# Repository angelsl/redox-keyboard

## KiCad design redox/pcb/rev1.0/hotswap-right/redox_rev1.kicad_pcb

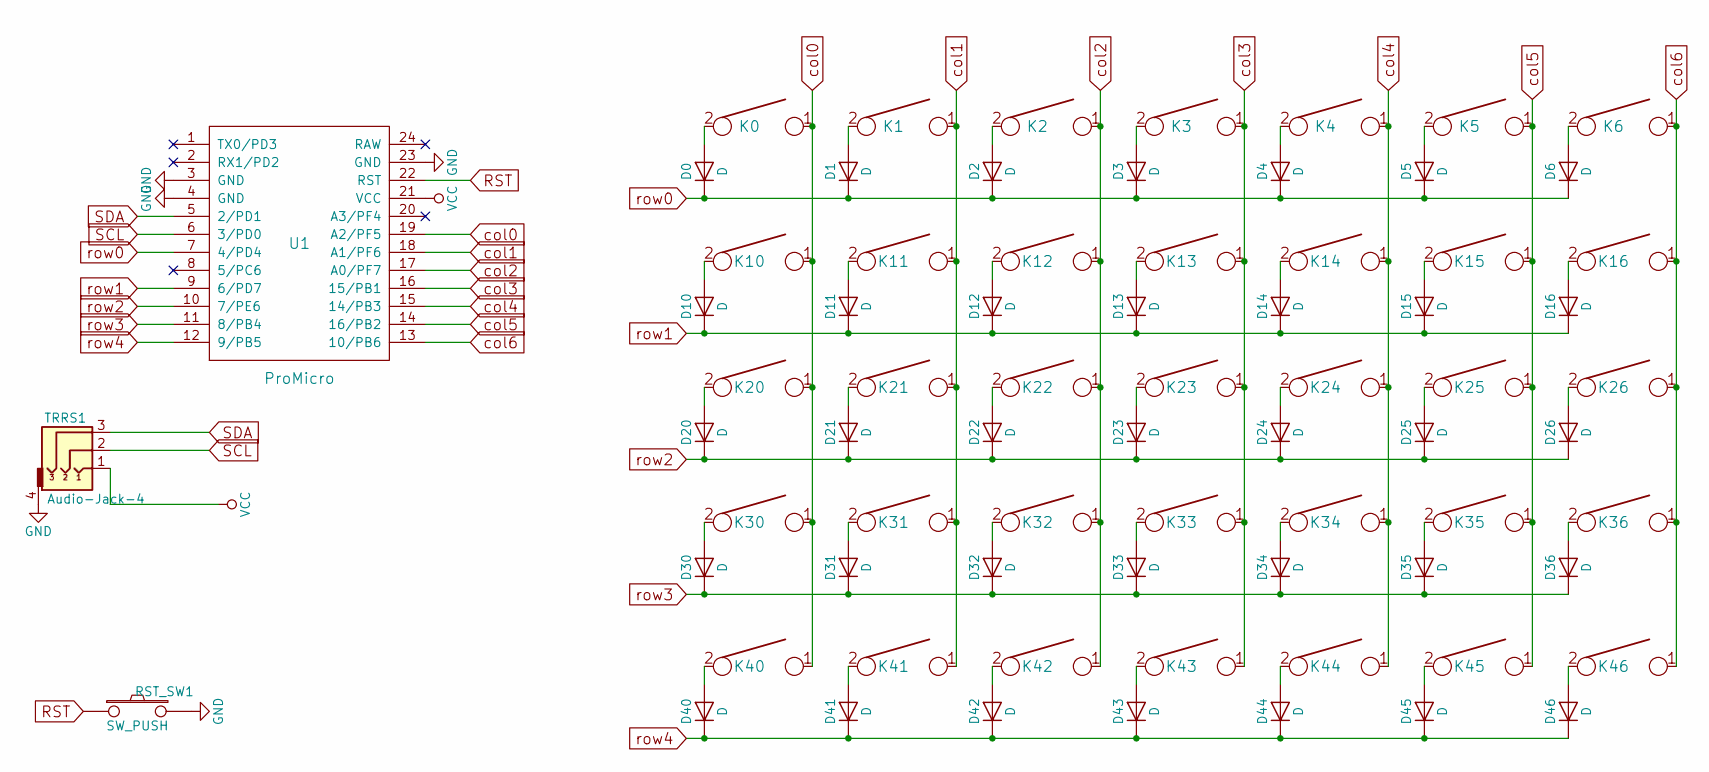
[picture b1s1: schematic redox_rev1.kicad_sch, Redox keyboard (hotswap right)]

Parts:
D0, D1, D2, D3, D4, D5, D6, D10, D11, D12, D13, D14, D15, D16, D20, D21, D22, D23, D24, D25, D26, D30, D31, D32, D33, D34, D35, D36, D40, D41, D42, D43, D44, D45, D46: D; Diode-smd-via
K0, K1, K2, K3, K4, K5, K6, K10, K11, K12, K13, K14, K15, K16, K20, K21, K22, K23, K24, K25, K26, K30, K31, K32, K33, K34, K35, K36, K40, K41, K42, K43, K44, K45, K46: KEYSW; Kailh_socket_MX
RST_SW1: SW_PUSH; SW_PUSH_6mm_h4.3mm
TRRS1: Audio-Jack-4; TRRS-PJ-320A-dual
U1: ProMicro; ArduinoProMicro

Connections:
GND: RST_SW1.2, TRRS1.4, U1.3 (GND), U1.4 (GND), U1.23 (GND)
unnamed: D0.2 (A), K0.2
unnamed: D1.2 (A), K1.2
unnamed: D2.2 (A), K2.2
unnamed: D3.2 (A), K3.2
unnamed: D4.2 (A), K4.2
unnamed: D5.2 (A), K5.2
unnamed: D6.2 (A), K6.2
unnamed: D10.2 (A), K10.2
unnamed: D11.2 (A), K11.2
unnamed: D12.2 (A), K12.2
unnamed: D13.2 (A), K13.2
unnamed: D14.2 (A), K14.2
unnamed: D15.2 (A), K15.2
unnamed: D16.2 (A), K16.2
unnamed: D20.2 (A), K20.2
unnamed: D21.2 (A), K21.2
unnamed: D22.2 (A), K22.2
unnamed: D23.2 (A), K23.2
unnamed: D24.2 (A), K24.2
unnamed: D25.2 (A), K25.2
unnamed: D26.2 (A), K26.2
unnamed: D30.2 (A), K30.2
unnamed: D31.2 (A), K31.2
unnamed: D32.2 (A), K32.2
unnamed: D33.2 (A), K33.2
unnamed: D34.2 (A), K34.2
unnamed: D35.2 (A), K35.2
unnamed: D36.2 (A), K36.2
unnamed: D40.2 (A), K40.2
unnamed: D41.2 (A), K41.2
unnamed: D42.2 (A), K42.2
unnamed: D43.2 (A), K43.2
unnamed: D44.2 (A), K44.2
unnamed: D45.2 (A), K45.2
unnamed: D46.2 (A), K46.2
RST: RST_SW1.1, U1.22 (RST)
SCL: TRRS1.2, U1.6 (3/PD0)
SDA: TRRS1.3, U1.5 (2/PD1)
VCC: TRRS1.1, U1.21 (VCC)
col0: K0.1, K10.1, K20.1, K30.1, K40.1, U1.19 (A2/PF5)
col1: K1.1, K11.1, K21.1, K31.1, K41.1, U1.18 (A1/PF6)
col2: K2.1, K12.1, K22.1, K32.1, K42.1, U1.17 (A0/PF7)
col3: K3.1, K13.1, K23.1, K33.1, K43.1, U1.16 (15/PB1)
col4: K4.1, K14.1, K24.1, K34.1, K44.1, U1.15 (14/PB3)
col5: K5.1, K15.1, K25.1, K35.1, K45.1, U1.14 (16/PB2)
col6: K6.1, K16.1, K26.1, K36.1, K46.1, U1.13 (10/PB6)
row0: D0.1 (K), D1.1 (K), D2.1 (K), D3.1 (K), D4.1 (K), D5.1 (K), D6.1 (K), U1.7 (4/PD4)
row1: D10.1 (K), D11.1 (K), D12.1 (K), D13.1 (K), D14.1 (K), D15.1 (K), D16.1 (K), U1.9 (6/PD7)
row2: D20.1 (K), D21.1 (K), D22.1 (K), D23.1 (K), D24.1 (K), D25.1 (K), D26.1 (K), U1.10 (7/PE6)
row3: D30.1 (K), D31.1 (K), D32.1 (K), D33.1 (K), D34.1 (K), D35.1 (K), D36.1 (K), U1.11 (8/PB4)
row4: D40.1 (K), D41.1 (K), D42.1 (K), D43.1 (K), D44.1 (K), D45.1 (K), D46.1 (K), U1.12 (9/PB5)

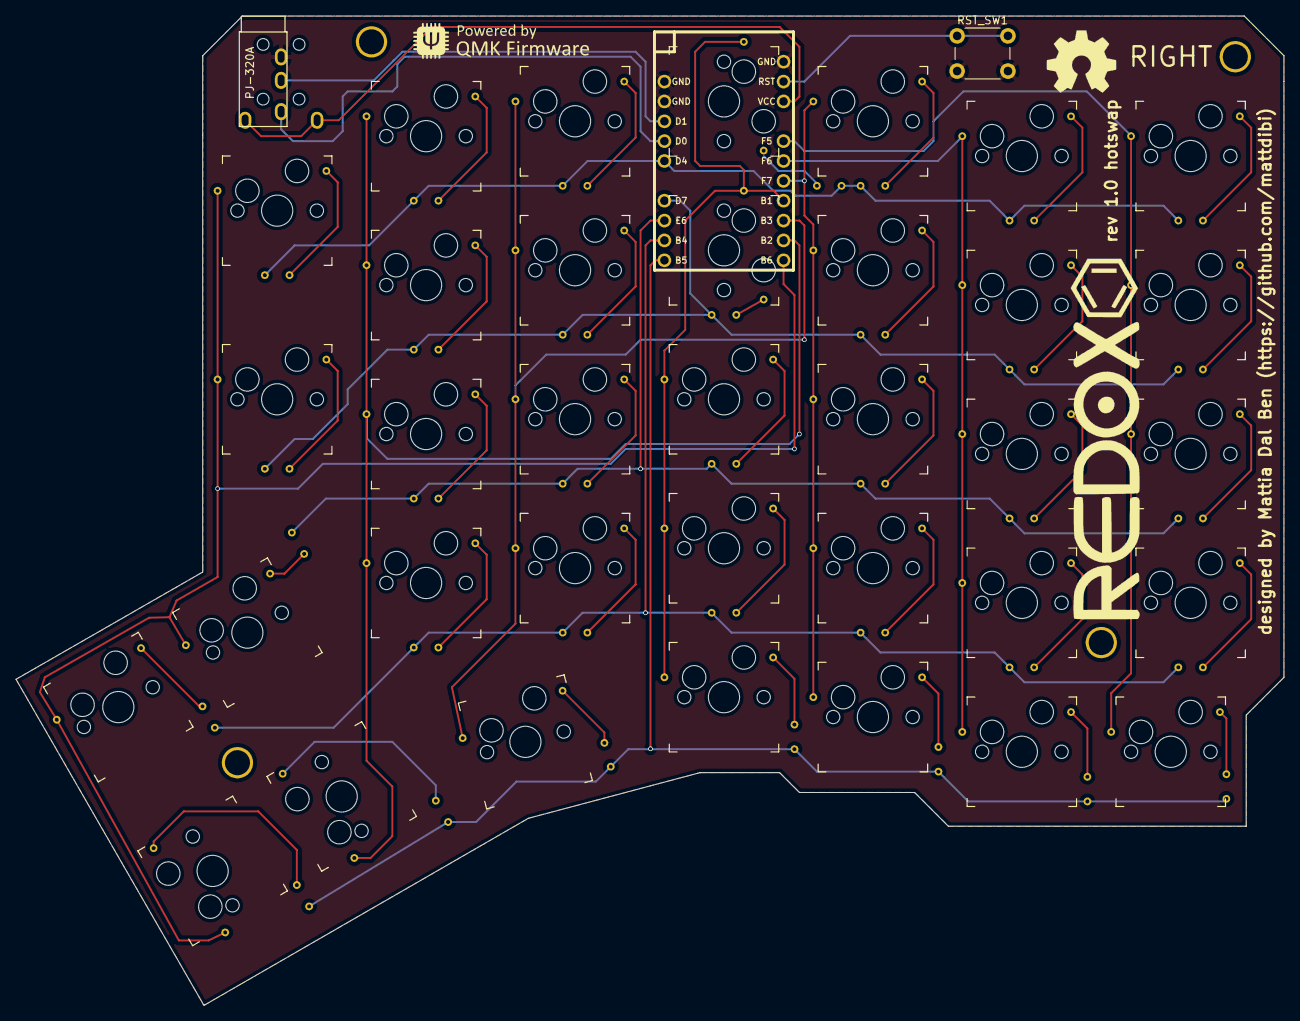
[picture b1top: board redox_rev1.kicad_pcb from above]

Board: 2 copper layers, 162.2 x 126.5 mm, 77 parts (0 on the bottom side), 52 nets.

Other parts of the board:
HOLE_M3, HOLE_M3#2, HOLE_M3#3, HOLE_M3#4: VAL**; HOLE_M3

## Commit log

2022-05-23 Add WIP Kailh hotswap socket PCB
2022-05-24 Route more nets
2022-05-26 Complete left PCB
2022-05-27 Add right PCB
2022-05-29 Remove pullup resistors from right schematic
2022-05-29 Complete right PCB
2022-05-29 Add 3D models to left PCB
2022-05-29 Add 3D models to some footprints
2022-05-29 Remove cache and local settings files and add .gitignore
2022-05-31 Add case with screw holes for PCB
2022-06-01 Increase switch hole size to 14.1mm
2022-06-12 Expand hole for PCB/port and cover gap above port
